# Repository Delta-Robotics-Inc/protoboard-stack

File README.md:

# Protoboard Stack

Protoboard is a framework for agents and people to design, check and release
hardware projects. A project describes its system in
[UHD](https://github.com/Delta-Robotics-Inc/uhd) (Universal Hardware
Description: modules, interfaces, links and harnesses, as TypeScript), and
Protoboard supplies the rest: project conventions, a parts library, checks,
a viewer, extensions that drive engineering tools (tscircuit and KiCad for
boards, build123d for CAD, Zephyr and ESP-IDF for firmware), skills that
teach an agent the workflow, and a release that ends in a Manufacturing
Package.

Think of it as "Next.js for hardware": initialize a project, add
capabilities as packages, work in VS Code with your agent, view the system
live, and cut a versioned hardware release. Any agent that speaks MCP or
reads `AGENTS.md` can use it; the stack does not run the agent.

This repository holds the stack: the framework core, the `protoboard` CLI,
the extensions, the viewer shells, the VS Code extension, the parts service
client, and the reference projects. It is open source under the [Apache
License 2.0](LICENSE).

## Install

Install the **Protoboard** extension in VS Code (Visual Studio Marketplace),
or in Cursor or Windsurf (Open VSX). It carries the whole stack and gives
your terminals the `protoboard` command, with no Node.js or npm needed. Or
install the command line alone (Node.js 22 or later):

```sh
npm i -g @protoboardai/cli
protoboard agents setup        # connect Claude Code, Codex, Cursor, … to the stack's MCP server
```

**[The installation guide](docs/guides/installation.md)** covers macOS,
Windows and Linux, each supported agent, your first project, signing in for
the Protoboard parts library (the only part that needs an account),
updating, uninstalling and troubleshooting.

## Quick start

```sh
protoboard init my-drone --template drone     # or wearable, iot; or a blank project
cd my-drone
protoboard check                              # every validator that can run; exit 1 on errors
protoboard dev --open                         # the viewer at http://127.0.0.1:5180/, live
protoboard release --check                    # what stands between the design and a release
```

Then open the folder in VS Code, or ask your agent to start from the
**build-a-project** skill. A project made with Protoboard 0.1 or 0.2 is moved
to 0.3 with `protoboard upgrade` ([release notes](docs/releases/stack-v0.3.md)).

## Documentation

- [Quickstart](docs/quickstart.md): a project from a template to a release, step by step.
- [Reference](docs/reference/README.md): the [CLI](docs/reference/cli.md),
  [configuration](docs/reference/configuration.md),
  [extensions and skills](docs/reference/extensions.md), the
  [Manufacturing Package format](docs/reference/manufacturing-package.md) and
  the [library protocol](docs/reference/library-protocol.md).
- Guides: [writing a capability provider](docs/guides/writing-a-capability-provider.md),
  [the SOP format](docs/guides/sop-format.md) every skill follows,
  [evals](docs/guides/evals.md), [a local registry](docs/guides/local-registry.md).
- Design: [architecture](docs/specs/architecture.md),
  [project structure](docs/specs/protoboard-project-structure.md),
  [UHD boundary](docs/specs/uhd-boundary.md),
  [tool integrations](docs/specs/tool-integrations.md),
  [distribution](docs/specs/distribution.md) and the rest of [docs/specs](docs/specs/).
- [Release notes](docs/releases/stack-v0.3.md).

## Repository layout

| Path | What |
| --- | --- |
| `packages/core` | `@protoboardai/core`: project loading, the definition registry, resolution, checks, build, templates, parts and libraries. |
| `packages/cli` | `@protoboardai/cli`: the `protoboard` command and its MCP server. |
| `packages/cloud` | `@protoboardai/cloud`: the typed client of the parts service and of any `uhd-library/v1` library. |
| `packages/views`, `packages/web-viewer` | The domain views and the shells of `protoboard dev` and the VS Code tabs. |
| `packages/ext-*` | The extensions: hardware, parts, sourcing, docs, release, drone, tscircuit, zephyr, esp-idf, frame-cad, harness-cad, enclosure-cad. |
| `packages/vscode-protoboard` | The VS Code extension ([developer reference](packages/vscode-protoboard/DEVELOPMENT.md)). |
| `examples/` | Reference projects: a 5-inch quadcopter, a wearable watch, a smart water bottle and a motor test bench. |
| `docs/` | The documentation above. |
| `scripts/` | CI, the lints, the local registry and publishing. |

## Developing

The stack builds against two repositories checked out beside it, UHD and the
viewer:

```sh
git clone https://github.com/Delta-Robotics-Inc/uhd.git
git clone https://github.com/Delta-Robotics-Inc/uhd-viewer.git
git clone https://github.com/Delta-Robotics-Inc/protoboard-stack.git
(cd uhd && npm install && npm run build)
(cd uhd-viewer && npm install && npm run build)
cd protoboard-stack && npm install
npm run typecheck && npm test
scripts/ci-stack.sh                 # the whole CI flow, as GitHub Actions runs it
```

[CONTRIBUTING.md](CONTRIBUTING.md) has the commands, the pull request
process and the sign-off; [docs/ci.md](docs/ci.md) the workflows.

## Licence and trademarks

The code is Apache-2.0 ([LICENSE](LICENSE), [NOTICE](NOTICE)); contributions
come in under the same licence with a DCO sign-off. "Protoboard" and its logo
are trademarks of Delta Robotics, Inc.; a fork you distribute needs its own
name ([TRADEMARKS.md](TRADEMARKS.md)).

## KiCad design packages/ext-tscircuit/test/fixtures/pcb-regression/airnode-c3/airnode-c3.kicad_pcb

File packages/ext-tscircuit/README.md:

# @protoboardai/ext-tscircuit

The first provider of the `circuit` capability
([tool integrations](../../docs/specs/tool-integrations.md)). It turns a UHD
board module into a routed PCB with [tscircuit](https://tscircuit.com), writes
the circuit capability's standard outputs, reads placements and frames back,
and checks the layout against the model. It runs inside Protoboard's own Node
process, offline.

A project selects it for one board, in the config next to the board module:

```ts
// src/boards/imu/circuit.config.ts
import { defineCapabilityConfig } from "@protoboardai/core";

export default defineCapabilityConfig({
  provider: "@protoboardai/ext-tscircuit",
  constraints: {
    layers: 2,
    thickness_mm: 1.0,
    outline: { circle: { diameter_mm: 30 } },
    mounting_holes: [{ id: "mount_left", at: [-11, -6], diameter_mm: 2.2 }],
    placements: { j1: { at: [0, 11.5], rotation_deg: 0 } }, // fixed by the enclosure
    keepouts: [{ name: "antenna", rect: { at: [0, -12], size: [8, 3] } }],
  },
});
```

```sh
protoboard run circuit:generate --module imu-tile-board
protoboard run circuit:export   --module imu-tile-board
protoboard run circuit:extract  --module imu-tile-board
protoboard check                # includes circuit:check for every bound board
```

The skill **circuit-board** (`skills/circuit-board/SKILL.md`) is the
procedure an agent follows: model the board, configure, generate, export,
extract, and act on each `CIRCUIT_*` finding.

`test/fixtures/imu-tile` is a complete example: an RP2040, a BMI270 and a
TPS63020 (test copies of UHD library parts in `test/fixtures/uhd-parts`, with
their origin noted there), with their decoupling, the regulator's inductor
and capacitors, and a JST SH header, on a 30 mm round board.

## How UHD maps to tscircuit

1. **Board netlist** (tool-neutral, in `@protoboardai/core`: `boardNetlist`).
   Each part on the board is a component with its UHD instance path, part
   id, kind, value, package facts and pin designators. A child that is a
   sub-module (`kind: "group"`, or children and no package or part number) is
   expanded: its parts are components under their paths (`led2/r1`), and its
   links join the board's (docs/specs/nested-boards.md); a child board or a
   daughterboard mated by connector stays off this PCB. Nets come from a
   union-find over the links of the board and its sub-modules between leaf
   pins and `Net` interfaces; a direct link between two functional ports
   (an I2C port to an I2C port) is copper, line by line as UHD pairs them.
   The board's exports are its edge. A KiCad or EasyEDA provider starts from
   the same step; only the land-pattern table and the writer differ.
2. **Source** (`lib/source.ts`). Each component becomes a `<chip>`,
   `<connector>`, `<resistor>`, `<capacitor>` or `<inductor>` named by its
   instance path. Its land pattern comes from the table below. Pad numbers are
   the part's designators; non-numeric ones (`EP`) follow the highest number.
   Each UHD pin is joined to its net by name (`<trace from=".u2 > .pin14"
   to="net.sda" />`). A pin with several pads (a module's grid of exposed
   ground pads) is one tscircuit port on its first pad and an internal port
   (`pinN_internal_k`) on each other pad; generate joins the pads to each other
   (see check), so every pad carries the net (`CIRCUIT_PAD_UNNETTED` otherwise). Supply, ground and no-connect pins get tscircuit pin
   attributes. Decoupling and pull-ups are components of the UHD board; the
   provider adds none.
3. **Constraints** (`lib/config.ts`). The outline (circle, rectangle or
   polygon; default: the board's `design_envelope`), mounting holes, keep-outs
   on each copper layer (an envelope keep-out takes `allow_bodies` from a
   config entry with its name and no shape), copper rules, and the positions the enclosure fixes
   (`pcbX`/`pcbY`/`pcbRotation`/`layer`; tscircuit does not move them). Later
   the enclosure's geometry manifest supplies the fixed positions.
   All of them are in the board frame (below), which is also the board
   module's own frame, so UHD regions on the board are read as they are. An
   outline taken from the `design_envelope` spans [0, length] × [0, width],
   the corner origin of UHD's example (`docs/boards-and-nets.md`). An envelope
   keep-out applies to each copper layer its z range reaches: top copper at
   z = +thickness/2, bottom at −thickness/2. A keep-out that misses the board,
   or reaches neither layer, is reported (`CIRCUIT_KEEPOUT`, warning) rather
   than silently doing nothing.
4. **Build** (`lib/runtime.ts`). The source is compiled with sucrase and
   rendered by `@tscircuit/core`: parts engine disabled, cloud autorouter off,
   a local autorouter preset (`auto_local` or `sequential_trace`). `fetch` is
   replaced during builds and exports by a guard that serves local files and
   refuses every network request.
5. **Stencil and silkscreen** (`lib/paste.ts`, `lib/silk.ts`), after every
   build. tscircuit prints paste at 70 % of each pad in each direction (49 %
   of its area), none on pill-shaped pads and on both sides of every plated
   hole; for every component with an authored land pattern those apertures
   are replaced by the pattern's own stencil (`paste`: 1:1 by default, a
   thermal pad's window-pane, none on bare test pads, pin-in-paste on plated
   slots on the part's side), placed and turned with the part. tscircuit draws
   silkscreen only for its built-in footprint strings, so each authored part
   also gets its reference (0.8 mm, else 0.6 mm, beside its courtyard where it
   clears every pad, hole, courtyard and the edge; a reference with no room is
   left off and logged) and a pin-1 dot. Paste apertures turned by other than a
   right angle are written to the paste Gerber as regions
   (circuit-json-to-gerber flashes them unrotated).

The provider directory, `src/boards/<module>/tscircuit/`:

| File | Owner | Content |
| --- | --- | --- |
| `board.gen.tsx` | generate (rewritten every time) | the generated source |
| `board.tsx` | you (written once) | the entry; wrap or replace the generated board here |
| `layout.json` | you | positions for parts the config does not fix: `{ <instance>: { at, rotation_deg, side } }` |
| `footprints.json` | you (optional) | land-pattern overrides: `{ packages: [entry…], instances: { <instance>: entry } }` |
| `circuit.json`, `build.json` | generate, export | the built board, the name map back to UHD, source and netlist digests, versions; `sourceFiles`, every file the build read besides the folder's own sources (JSON a hand file imports, a hand file in another folder), which the source digest covers |
| `models/` | export | box bodies for parts without a body artifact; copies of part bodies without their interface feature shapes |

**Bodies and supplier numbers in the source.** Generate writes each
component's body into `board.gen.tsx` as a `cadModel`: the part's STEP (the
copy in `models/` without its interface feature shapes), else its GLB or OBJ
(UHD GLBs are glTF metres, +Y up: `modelUnitToMmScale: 1000`,
`modelBoardNormalDirection: "y+"`), with the mount origin as
`modelOriginPosition`. Paths are relative to the `tscircuit/` folder with
forward slashes, so they mean the same on every OS and machine; no
`tsci dev` URL is ever written. tscircuit itself centres a model on the pads;
the provider's exports place every body by its mount frame on a copy of the
circuit JSON (below). Each component also gets `supplierPartNumbers` from the
offers the project holds (`parts/offers.json`, `parts/evidence/<part>/sourcing.json`),
for its own MPN, LCSC first (JLCPCB assembles from LCSC numbers), then DigiKey
and Mouser; they are generate inputs, so new offers make the board stale until
the next generate.

**Land patterns by package family.** An entry matches a package by its
normalised name, else by its family: `SOT-23-5`, `SOT23-5` and `SOT23-5L` are
one; `0402 (1005 metric) chip` is the 0402 chip; `QFN-32-EP`, `VQFN-32` and
`WQFN32` are `qfn-32`; `VSSOP-10` is `msop-10`. Either way every fact the entry
states (pin count, pitch, body size, maker) must agree. A family match is
reported (`CIRCUIT_FOOTPRINT_FAMILY`, info); a package whose name or family
has entries that do not fit is reported with why (`CIRCUIT_FOOTPRINT_MISMATCH`)
and generate stops on it, instead of picking one.

Parts missing from both the config and `layout.json` are placed by
tscircuit's packer. It fails on dense boards ("Unable to pack all PCB
components"), and placement errors stop routing; generate then fails and says
so. Add positions to `layout.json` and generate again.

## Standard outputs

Under `out/`, replaced by every export. The export writes into a staging
folder beside it (`.out.staging`), and core swaps the files in only when the
export succeeds: a failed export (a converter that throws) leaves the last
good `out/` in place, and nothing reading `out/` sees it half written:

| File | Content |
| --- | --- |
| `gerber/*.gbr`, `gerber/*.drl` | Gerber RS-274X with X2 attributes (copper, mask, paste, silk, `Edge_Cuts`) and Excellon (plated, non-plated). Creation timestamps are removed, so an unchanged board exports identical files. |
| `bom.csv` | `instance, part, name, kind, manufacturer, mpn, value, package, quantity, lcsc, supplier_part_numbers`, one row per component (`supplier_part_numbers`: `lcsc:C… digikey:… mouser:…`). tscircuit's own BOM lacks the MPN and is keyed by refdes, so it is not used. |
| `pnp.csv` | `instance, x_mm, y_mm, rotation_deg, side, part, mpn, package, lcsc`, at the pad bounding-box centre. |
| `jlcpcb/bom.csv`, `jlcpcb/cpl.csv` | The same parts in JLCPCB's assembly upload format, by reference designator (`refdes.json`, as the silkscreen prints them). BOM: `Comment, Designator, Footprint, LCSC Part #`, one row per part with its designators grouped; the LCSC number comes from the project's offers only and is left empty (and listed in the export's summary data, `withoutLcsc`) when there is none. CPL: `Designator, Mid X, Mid Y, Layer, Rotation`, mm with the unit, `Top`/`Bottom`, in the Gerbers' frame. Rotation is the layout's (counter-clockwise from the top): no correction for JLC's library orientation is applied, so check polarized parts in JLC's placement preview. A locked board writes them from KiCad's position file. |
| `board.glb` | glTF binary in glTF's own convention (metres, +Y up), like every other UHD body. One root node `board` maps tscircuit's frame to it; component nodes are named by instance path. |
| `board.step` | AP214, mm, board frame. One mapped item per component, named by instance path; model representations are named by artifact (`<part>#<artifact>`) or project-relative box path, and the header date is fixed, so an unchanged board exports an identical file. |
| `board.manifest.json` | UHD geometry manifest: `outline` (the underside), `board_top`, each mounting hole by its config id, each component by instance path, each board export by its id. Every feature also carries `frame` (origin, normal, xAxis). |
| `netlist.json` | `protoboard.netlist/v0`: the nets as the copper joins them, named by the UHD net each piece carries (`scl+sda` when a piece carries two). |
| `schematic.svg`, `pcb-top.svg`, `pcb-bottom.svg` | renders for the viewer. |

**Board frame:** mm, +X right and +Y up in the top view, +Z out of the top
copper, z = 0 on the board's mid-plane (tscircuit's convention). The top
surface is z = +thickness/2.

**Bodies** in `board.glb` and `board.step`, per component: the part's own UHD
body artifact (STEP), placed on the board by the part's mounting frame (the
interface facing −Z); else a box from the part's package facts
(`dimensions_mm`); else tscircuit's generated body for a built-in footprint,
or none. Export reports which one each component got, and names every body
`board.glb`'s converter could not load (it draws a box in its place; an
unfetched Git LFS file, say) instead of counting it as a body. Model files are
read through the offline guard, which takes absolute paths and `file://` URLs
on every platform (on Windows `C:\…`, `C:/…`, UNC paths and `file:///C:/…`). In both files a body's
origin goes to the footprint centre on the board surface (z = ±thickness/2).

UHD CAD bodies carry one named sub-shape per interface feature (thin marker
solids on the faces an interface binds to; for an SMD part, 0.25 mm under its
seating plane). They are not part of the body, so export writes a copy of the
part's STEP without the sub-shapes named after the part's interfaces, under
`models/`, and uses that.

`circuit-json-to-step` 0.0.43 places a model by recentring it on the bounding
box of every point in its file (axis placements included) and lifts it by
half the board thickness above a position that is already the board surface.
Export sets each mapped item's origin back to the component's position
afterwards, keeping the converter's axes. The test resolves every body's
world bounding box in `board.step` and checks it against the pick-and-place
centre and the board top.

## extract

Frames for the board's exports and interfaces, taken from the manifest
features of the same id: a connector's frame is its mouth, with the mating
direction as the normal; a component's is the top of its body; a pin export's
is its pad. A mechanical interface of the board binds to its underside. Also
the artifacts to reference (outputs and the native source, `format:
"tscircuit"`) and, outside UHD, the placements, outline and routing totals.
Writing frames into the module is a separate step, as for CAD.

## check

Pure: it reads the last build and writes nothing.

| Code | Severity | Finding |
| --- | --- | --- |
| `CIRCUIT_NOT_BUILT` | info | no build yet |
| `CIRCUIT_BOARD_GROUPING` | warning | a sub-module's export the board leaves unconnected (not marked `unconnected` on the child), or a sub-module with no parts |
| `CIRCUIT_STALE` | warning | the native source changed since the build (export rebuilds); the UHD board changed since generate; or `layout.json`, `footprints.json` or the config's constraints changed since generate (generate bakes them into `board.gen.tsx`, so only generate catches up; export says so in its summary); or `out/` was exported from other inputs than the current ones (the built board, what the board depends on in UHD, a body file, the provider's code, a converter version: `tscircuit/export.json` records what each export read, and the message names what changed), or by an earlier provider that kept no such record. What the board depends on is a projection of the board module: its components (part, name, maker, MPN, value, package, pins, bodies and mount frames, the interface ids stripped from bodies), nets, edge and the edge parts' mating frames, and its design envelope; descriptions, prices and documents are not in it, so editing them does not make `out/` stale. The constraints (outline, mounting holes, keep-outs) are fingerprinted with the config. Export is reproducible: the same inputs give the same `board.step` and `board.glb` |
| `CIRCUIT_DRC` | error | an error tscircuit recorded while building, or one `@tscircuit/checks` finds |
| `CIRCUIT_NET_OPEN`, `_SHORT`, `_EXTRA`, `CIRCUIT_UNROUTED`, `CIRCUIT_PIN_MISSING` | error | the copper's nets differ from the UHD nets (core's `netlistDrift`) |
| `CIRCUIT_PAD_UNNETTED` | error | a pin with several pads has pads the copper does not join to its net (boards generated before 0.1.7 netted only the first pad: the smart-bottle and wearable-watch ESP32-C3 ground pads) |
| `CIRCUIT_FINGERPRINT_FORMAT` | info | `tscircuit/export.json` is from a provider that fingerprinted the whole UHD module; such a record is not compared for the board (no false stale) until the next export writes the new format |
| `CIRCUIT_FOOTPRINT_FAMILY` | info | a land pattern chosen by the package's family, its facts agreeing |
| `CIRCUIT_FOOTPRINT_MISMATCH` | error | land patterns of the package's name or family exist but none fits its pin count, pitch or size (reported, not guessed) |
| `CIRCUIT_VIA_TOUCHING_PAD`, `CIRCUIT_VIA_UNDER_BODY` | error | a via whose ring touches an SMD pad / a via inside a courtyard, when `via_touching_pad` / `via_under_body` is `avoid` |
| `CIRCUIT_HOLE_CLEARANCE` | error | copper nearer a non-plated hole's wall than `rules.hole_clearance_mm`, or inside it; round holes are circles, pill holes stadiums, never bounding boxes |
| `CIRCUIT_TRACE_WIDTH` | warning | a net routed narrower than `trace_widths` asks |
| `CIRCUIT_COMPONENT_MISSING`, `_EXTRA` | error | a UHD component is not on the board, or the board has one UHD lacks |
| `CIRCUIT_OUTSIDE_OUTLINE` | error / warning | a pad off the board / a body overhanging the edge |
| `CIRCUIT_KEEPOUT` | error / warning | pads, traces or vias inside a keep-out on its layer / a keep-out off the board or reaching neither copper layer |
| `CIRCUIT_PLACEMENT_MOVED` | error | a part the config fixes is somewhere else |
| `CIRCUIT_FOOTPRINT_UNVERIFIED` | warning | a land pattern the board uses has no verification record against its maker's recommended land pattern, or its pads, pitch, rows, slots, holes, courtyard, paste or mask differ from the record (`verifyEntry`, below); the work order then opens with a hold |
| `CIRCUIT_VIA_RULES` | error | a via whose pad or drill is smaller than `rules.via_pad_mm` / `rules.via_drill_mm` (the router keeps to them; a via written by hand may not). A locked board's KiCad project carries the same minimums as custom rules (`<board>.kicad_dru`), so KiCad's DRC finds them too |
| `CIRCUIT_HAND_PAD_JOIN` | warning | a trace written by hand (in `board.tsx`) joins pads of one pin, which generate joins itself since 0.1.7; in KiCad it becomes copper on no net. Remove it. generate logs the same |
| `CIRCUIT_VIA_IN_PAD` | error / info | a via inside an SMD pad / the same with `via_in_pad: "fill_and_cap"` (the order asks for IPC-4761 type VII) |

Every finding carries a `location` (core's `DiagnosticLocation`): `at` (mm,
board frame) and `points` where it has several, the copper `layer`, and the
`components`, `pads` (circuit.json pad ids), `nets` and other copper `items`
(traces, vias, holes, pours, keep-outs) it concerns; a finding about the whole
board has `scope: "design"`. The PCB view draws findings there.

A pin with several pads (a module's grid of exposed ground pads) is joined pad
to pad by the shortest tree over the SMD pads: a join clear of the part's
other pads is straight copper laid on the built board after routing (so it
cannot change the routing), any other is a routed trace. A pin's plated holes
(a receptacle's shell stakes) are joined by the part's own metal and not by
copper.

A body overhanging the edge is judged by its courtyard as placed (turned
with the part), not its axis-aligned box; a part the native entry lets off the
board (`allowOffBoard`: a mid-mount receptacle in its cut-out) is not reported
for its body, and its pads still are.

The copper netlist is built from `pcb_*` elements only. The connectivity
map's full mode also merges the source intent, which would make an unrouted
net look connected (spike §4).

## Land-pattern table

`lib/land-patterns.ts` (the table), `lib/land-geometry.ts` (the entry format),
`lib/footprints.ts` (lookup and verification). UHD parts state their package
as the manufacturer prints it; which copper fits that package is the
provider's knowledge, kept here and never written into a part. An entry
matches a package by name, and when it says so by pin count, pitch, body size
and maker (`match.manufacturer`, a case-blind prefix of the part's
manufacturer: Murata and Yageo recommend different 0402 lands). Names are
compared without case, spaces, underscores or dashes, and `×` reads as `x`.
An entry's frame is the part's mounting frame, so the copper and the part's
3D body agree.

**Verification.** An authored entry carries a `verification` record: the
document, page and figure it was read from, the date, and the values the
drawing gives, transcribed independently of the pads: pad groups (pins, size
or a range the drawing allows, pitch, row spacing; `merged` for paired
contacts that share one land, drawn as two touching halves so each designator
has a pad), optionally every pad centre the drawing dimensions, plated slots
(drill and ring), round holes (plated with their pad, or not), each with the
centres the drawing puts them at (`at`, so a moved slot or peg is caught), the courtyard,
the stencil (margin, window counts and sizes, coverage, pins with none,
pin-in-paste) and the mask margin. `verifyEntry` compares the copper with the
record; an entry is verified when it has a record and nothing differs.
`circuit:check` reports every land pattern a board uses that is not verified
(`CIRCUIT_FOOTPRINT_UNVERIFIED`), and the board's work order states how many
are verified and opens with a hold while any is not. Built-in footprint
strings cannot be verified (their copper is not stated in the entry).

| Entry | Package (maker) | Drawing |
| --- | --- | --- |
| `yageo-rc0402-reflow` | 0402 (Yageo) | Chip Resistors Mounting, Table 1 |
| `murata-grm15-reflow`, `murata-grm18-reflow` | 0402, 0603 (Murata) | GRM specification sheets, Land Dimensions Table 2: one land inside both tolerance rows |
| `lga-14-3x2.5-p0.5-bosch` | LGA-14 3.0 × 2.5 (BMI270) | BST-BMI270-DS000-08 §8.3 |
| `vson-14-dsj-4x3-p0.5` | VSON-14 DSJ (TPS63020) | 4210895-2/E with its stencil (four windows on the thermal pad), 4208549-3/G |
| `ti-dbv0005a`, `ti-dgs0010a`, `ti-rsm0032b` | SOT-23-5, VSSOP-10, VQFN-32 (TI) | 4214839/K, 4221984/A, 4219108/B (thermal pad stencil 4 × 1.23 mm, 77 %) |
| `microchip-c04-2091-ot`, `microchip-c04-2123b-mc` | SOT-23-5, DFN-8 2 × 3 (Microchip) | C04-2091-OT Rev F, C04-2123B |
| `maxim-90-0065-tdfn8`, `maxim-90-0602-olga14` | TDFN-8 2 × 2, OLGA-14 (Analog Devices/Maxim) | land patterns 90-0065 rev E, 90-0602 rev F |
| `st-sot23-6l`, `st-vl53l4cd-lga12` | SOT23-6L, Optical LGA12 (ST) | DS4260 Figure 19; DS13812 Figure 19 (pads 1:1: ST gives no separate land) |
| `aos-sot23-po00001` | SOT23 (AOS) | PO-00001 rev N |
| `coilcraft-xfl4020`, `epson-fc-135`, `kingbright-aptf1616` | XFL4020, FC-135, APTF1616 | 745-3, FC-135_E_Ver2.0 [7], DSAO4453 |
| `alps-skrt-guide-bosses` | SKRT side-push switch (Alps) | SKRT catalog Drawing No.1 (guide-boss holes Ø0.9 NPTH) |
| `gct-usb4720-midmount`, `gct-usb4105-topmount` | USB-C receptacles (GCT) | USB4720 rev B, USB4105 rev B4 (plated stake slots, tag holes or peg holes, paired contacts on one land) |
| `espressif-esp32-c3-mini-1`, `raytac-mdbt50q` | modules | ESP32-C3-MINI-1 v2.2 Figure 11-1 (3 × 3 ground pads); MDBT50Q-1MV2 Ver. L §2.2 (every pad centre) |
| `eastrising-er-tft128-1-fpc` | ER-TFT1.28-1 FPC tail | the tail's contacts (the maker gives no board land) |
| `qfn-56-7x7-p0.4-ep3.2` | QFN-56 (RP2040, test fixture) | RP2040 datasheet Figure 167; no record yet (unverified) |
| `builtin-0201` … `builtin-1206`, `builtin-sot23`, `builtin-sot23_5`, `builtin-jst4_p1mm_sh` | chip passives and SOT-23 from makers with no entry; JST SH | tscircuit footprinter (built in); unverified |

Authored entries are lists of pads (designator, centre, size; top view, mm),
non-plated holes, plated holes and slots (`drill` in a pad), the courtyard
(`courtyard_mm`, centred on `courtyard_at`), the stencil (`paste`) and the
mask (`mask`). Where the drawing gives no courtyard, mask or stencil the
record says what was used (IPC-7351B nominal courtyard 0.25 mm beyond pads,
holes and body; NSMD mask 0.05 mm; paste 1:1). For built-in entries, generate
checks that the pattern has a pad for every pin designator. A project adds or
overrides entries in `tscircuit/footprints.json`, for a package or one
instance, with the same record (board copper designed in the project cites
the pad part that states it). A part with no package fact, or a package with
no entry, stops generate with a message saying which.

## Routing controls

Constraints in `circuit.config.ts`, beside `layers`, `rules` and `autorouter`:

| Constraint | Effect |
| --- | --- |
| `routing` | `on` (default) or `off`: the board is placed but not routed (`routingDisabled`). Check reports the unrouted nets, unconnected ports and unjoined pads as info, not errors: a placement-only board for review or a hand route |
| `trace_widths` | `{ nets?: { <UHD net id>: mm }, classes?: { signal?, power?, ground?: mm } }`: each net's `nominalTraceWidth` is its own width, else its class's, else the rules' (`power_trace_width_mm` for power and ground nets). A net id the board lacks stops generate. Check reports a net whose narrowest routed segment is narrower than asked (`CIRCUIT_TRACE_WIDTH`, warning: the router necks down where the width does not fit) |
| `via_in_pad` | `avoid` (default; the router keeps vias out of SMD pads, `isViaInPadAllowed` off) or `fill_and_cap` |
| `via_touching_pad` | `allow` (default) or `avoid`: no via ring touching an SMD pad it does not sit in. tscircuit's router has no such rule, so it is checked only (`CIRCUIT_VIA_TOUCHING_PAD`) |
| `via_under_body` | `allow` (default) or `avoid`: no via inside a component's courtyard. Checked only (`CIRCUIT_VIA_UNDER_BODY`) |
| `rules.hole_clearance_mm` | least distance from a non-plated hole's wall to any copper (pads, plated holes, vias, traces, pours). Checked (`CIRCUIT_HOLE_CLEARANCE`); without it, only copper inside a hole is reported. Round holes are circles, not bounding boxes |

## KiCad: preview, lock and unlock

KiCad is the final hand-placement step ([spec](../../docs/specs/pcb-kicad-handoff.md)):
tscircuit is the layout of record while the design changes, KiCad after a
person locks the board.

```sh
protoboard run circuit:kicad  --module <board>   # KiCad 10 project of the current build in tscircuit/kicad/ (a preview)
protoboard run circuit:lock   --module <board>   # the project into <board dir>/kicad/ + handoff.json: KiCad is the layout of record
protoboard run circuit:unlock --module <board>   # kicad/ to kicad-archive/<stamp>/; tscircuit again
```

The project (`lib/kicad/`): tscircuit's `circuit-json-to-kicad` 0.0.237 (MIT)
writes the board, schematic and project from `circuit.json`; the provider
renames components to their reference designators first and sets the part
bodies as export does, then edits the result: the board's own footprint and
symbol libraries (`<board>.pretty`, `<board>.kicad_sym`, `fp-lib-table`,
`sym-lib-table`), bodies copied to `3d/` and linked through `${KIPRJMOD}`,
`MPN`, `Manufacturer`, `LCSC` (from `parts/offers.json`), `UHD_Instance` and
`UHD_Part` on every symbol and footprint, symbols and footprints linked by
UUIDs derived from the instance paths, pads turned with their footprint,
mounting holes as board-only footprints `H1…`, pads that share a netted pad's
number given its net, KiCad's `unconnected-(…)` nets on unconnected pins, a
global label with the board's net on every connected schematic pin (the
converter's wires do not always reach the pins), the config's layers,
thickness, stack-up and edge clearance, and the board frame's origin as the
drill/place origin. `kicad-cli pcb upgrade` / `sch upgrade` then save both in
KiCad 10's format. On the smart-bottle board KiCad's DRC finds no
schematic-parity problem in the exported project, and its ERC only the
board's own power-flag findings.

Reference designators (`lib/kicad/refdes.ts`) are kept per instance in
`tscircuit/refdes.json`: an id that already reads as a designator of its
kind (`r3`) keeps it, others take the kind's prefix and the lowest free
number; a removed instance keeps its designator reserved.

After lock, `circuit:generate` refuses without `--force`, `circuit:export`
makes `out/` with `kicad-cli` (DRC first, into `out/drc.json`; an error stops
the export without `--force`; Gerber and Excellon, the position file re-keyed
by UHD instance, STEP and GLB with the part bodies, SVG renders, the copper
netlist; the BOM from the model; the manifest from the build at lock with
component positions from KiCad), and `circuit:check` compares the model, the
handoff record and the KiCad files (`CIRCUIT_LOCKED`, `CIRCUIT_KICAD_*`, spec
§4). Check runs `kicad-cli sch export netlist` on a copy when KiCad is
installed (it writes nothing into the project) and reads the board file
itself otherwise.

Known limits: the GLB and STEP from KiCad are in KiCad's frame (board bottom at
z = 0, not the mid-plane); a component turned in KiCad keeps tscircuit's
orientation in the manifest; footprints at angles other than right angles may
differ from their library copy (`lib_footprint_mismatch`, a warning).

## In the Manufacturing Package

With @protoboardai/ext-release, `protoboard release` calls `package:work-order`
(`ops/package.ts`) for each unit that builds a board this provider designs.
It adds the board's fabrication and assembly order: quantity, layers,
thickness, copper, surface finish, solder mask and silkscreen, the stack-up
for the layer count, assembly sides and placements from `out/pnp.csv`, the
leadless packages (from the parts' package names) that want a stencil and
X-ray inspection, and the files to send. These order values are optional
constraints in `circuit.config.ts`; the order marks the defaults it used:

| Constraint | Default |
| --- | --- |
| `copper_oz` | the fab's standard (1 oz outer) |
| `finish` | ENIG when any part is leadless (QFN, DFN, LGA, BGA, CSP, SON), else lead-free HASL |
| `solder_mask`, `silkscreen` | green, white |
| `assembly` | `fab` (the fab places from `pnp.csv`); `hand` |
| `fab_notes` | none: a list of notes for the fab, numbered on the order after the provider's own |
| `via_in_pad` | `avoid`: the router keeps vias out of SMD pads, and check reports any as an error; `fill_and_cap` allows them and adds the fill-and-cap note (IPC-4761 type VII) |

The order's own notes come first: a hold while any land pattern the board
uses is unverified (naming them), and the fill-and-cap note when vias sit in
pads under `via_in_pad: "fill_and_cap"`. It also states how many land
patterns are verified and how many vias are in pads.

They do not change the design, but they are inputs to it, so changing one
makes `check` report the board stale until it is regenerated. They are
validated with the other constraints (`copper_oz` a positive number;
`finish`, `solder_mask`, `silkscreen` non-empty strings; `assembly` exactly
`fab` or `hand`; `fab_notes` a list of non-empty strings): `generate` refuses a bad value and `check` reports it as
`CIRCUIT_CONFIG_INVALID`.
`test/package.test.ts` checks the order, and the release's bring-up checks
for a custom board, on the IMU tile.

## Licensing

- tscircuit's libraries are MIT, `@tscircuit/footprinter` ISC (the built-in
  footprint strings are generated locally by it), `circuit-to-svg` ISC.
  `@tscircuit/checks` publishes no licence field or file (spike, Versions).
- **KiCad footprint and 3D-model libraries are not bundled and not fetched.**
  They are CC-BY-SA 4.0; shipping converted footprints as a set inside this
  Apache-2.0 provider would mix a share-alike collection into it. The
  authored entries are drawn from the manufacturers' recommended land
  patterns instead. A user may add footprints they hold the rights to in
  their project's `footprints.json`.
- Component bodies come from the project's own UHD parts, or are boxes.
- `circuit-json-to-kicad` and `kicadts` are MIT (tscircuit). The KiCad skills
  (`kicad-layout-review`, `kicad-cli`) are derived from KiStack (MIT); see
  `NOTICE`. KiCad itself is not bundled: `kicad-cli` is a declared tool.

## Tools and versions

Declared as the tool `tscircuit-node` (`protoboard doctor` probes it with
`lib/probe.cjs`): every tscircuit package is pinned to an exact version in
`package.json`, because they release `0.0.x` versions daily. An upgrade is a
deliberate change, checked by this package's end-to-end test.

- `@tscircuit/core` 0.0.2056, `@tscircuit/checks` 0.0.233,
  `@tscircuit/footprinter` 0.0.430, `circuit-json-to-gerber` 0.0.111,
  `circuit-json-to-gltf` 0.0.141, `circuit-json-to-step` 0.0.43,
  `circuit-to-svg` 0.0.438, and core's peers at the spike's versions.
- `circuit-json-to-gerber` declares the `tscircuit` meta-package (with the
  `tsci` CLI) as a peer. The repository's `.npmrc` sets
  `legacy-peer-deps=true` so that npm does not install it: it is never run,
  and its own nested copies of `@tscircuit/core` broke module resolution in
  the workspace. Missing peers are listed in `package.json` instead.
- **Projects outside the workspace** (installed from the registry, without
  the repository's `.npmrc`) need the workspace's `legacy-peer-deps=true` in
  their own `.npmrc` (some tscircuit packages import `circuit-json` without
  declaring it, so it must be at the top level) and
  `"overrides": { "circuit-json": "0.0.510" }` in `package.json`
  (`@tscircuit/checks` and `@tscircuit/core` take it as a peer; an older
  hoisted copy stops the checks: `CIRCUIT_DRC` "@tscircuit/checks did not
  run"). The templates that use this extension write both; keep the override
  equal to the pin above (`packages/core/test/templates.test.ts` checks the
  templates and examples).
- **Node.** Developed on Node 24.14.1. The full contract (generate, export,
  extract, check of the test board) also passed on Node 22.23.3, although
  `circuit-to-svg` declares `engines.node: 24.x`.
- `tsci` and Bun are not used. tscircuit's route cache is not used either.
  Agents never run `tsci dev`, `tsci build` or `tsci export` on a board this
  provider owns: tsci rebuilds it with another core, re-routes it, and its
  watcher crashes on files generate and export rewrite (seen on a large field
  project). The
  Protoboard viewer shows `out/`. The skill's `references/pcb-workflow.md`
  has the workflow, how to get KiCad files until the provider writes them
 , and the fallback policy.
- One build of the test board (21 parts, 12 nets) takes about 35 s and 1.2 GB.

## Limits

- **Fabrication needs a second DRC.** tscircuit's rules are looser than a
  fab's; the spike found same-net vias 0.1 mm apart and exporter defects that
  only KiCad's DRC reports (spike §6). Defaults here are 0.15 mm traces and
  0.3/0.6 mm vias; review before ordering. Nothing is uploaded or ordered.
- **Routing quality.** Routes are complete, not tidy: detours and many vias.
  Hand polish belongs in `board.tsx` (`<tracehint>`, `<pcbtrace>`).
- **Placement** is hand-assisted: dense boards need `layout.json`.
  Bottom-side parts and model offsets on rotated parts are untested.
- **Bodies.** Only STEP body artifacts are used (GLB-only parts get a box). A
  part's mounting frame is assumed to face −Z with its X axis along the
  footprint's X.
- **Manifest `frame`.** UHD's `GeometryManifest` has no `frame` per feature
  yet; it is written as an extra field, proposed for UHD (spike §9).
- **Fixed placements** are written in the config today; reading them from the
  enclosure's manifest is the `cad` provider's follow-up.
- The test board is a routing and export load, not a reviewed design: see
  the fixture's header comment for what it leaves out.

## Evals

`evals/catch-swapped-nets`: the IMU tile's tscircuit source is hand-edited
(SDA and SCL swapped on the BMI270); the agent rebuilds the board, names the
fault and restores a board that matches the model. Its fixture builds the
board once and the solution twice (about 2 minutes, 1.2 GB per build). `evals/generate-imu-board`: a board never built, with a fault in its model to
catch first. `evals/announce-pcb-fallback`: KiCad files wanted today for a
hand finish, which the provider cannot write yet; the agent must announce
that it is leaving the official path, why and at what cost, record it in the
worklog and as feedback, and leave the model, `out/` and the provider's files
alone. Run them with `protoboard evals --extension tscircuit`; see the
[evals guide](../../docs/guides/evals.md).

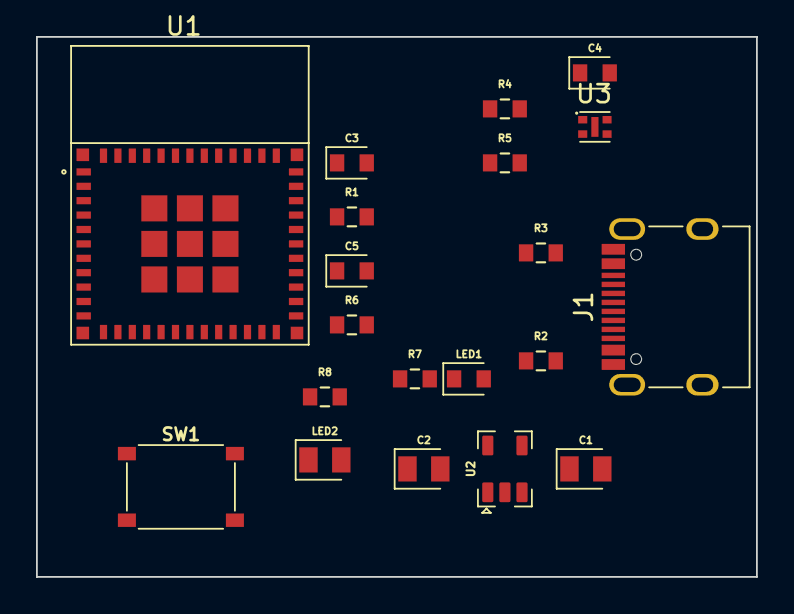
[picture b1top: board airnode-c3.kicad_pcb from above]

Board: 2 copper layers, 40.0 x 30.0 mm, 20 parts (0 on the bottom side), 15 nets, no tracks yet.

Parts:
C1, C2: 10uF; capacitor_cap0805
C3, C4: 100nF; capacitor_cap0603
C5: 1uF; capacitor_cap0603
J1: TYPE-C-31-M-12
LED1: LED; led_0603_color_red
LED2: LED; led_0805_color_green
R1, R6: 10kΩ; resistor_res0603
R2, R3: 5.1kΩ; resistor_res0603
R4, R5: 4.7kΩ; resistor_res0603
R7, R8: 1kΩ; resistor_res0603
SW1: SW1; TS-1187A-B-A-B
U1: ESP32-C3-MINI-1-N4
U2: AP2112K-3.3TRG1; AP2112K-3_3TRG1
U3: SHT40-AD1B-R2

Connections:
.J1 > .CC1 to .R2 > .pin1: J1.6, R2.1
.J1 > .CC2 to .R3 > .pin1: J1.12, R3.1
.R1 > .pin2 to .U1 > .EN: C5.1, R1.2, U1.8
.R6 > .pin2 to .U1 > .IO8: R6.2, U1.22
.R7 > .pin2 to .LED1 > .anode: LED1.1, R7.2
.R8 > .pin1 to .U1 > .IO7: R8.1, U1.21
.R8 > .pin2 to .LED2 > .anode: LED2.1, R8.2
.SW1 > .A to .U1 > .IO9: SW1.1, U1.23
GND: C1.2, C2.2, C3.2, C4.2, C5.2, J1.13, J1.14, LED1.2, LED2.2, R2.2, R3.2, SW1.3, U1.1, U1.2, U1.11, U1.14, U1.36, U1.37, U1.38, U1.39, U1.40, U1.41, U1.42, U1.43, U1.44, U1.45, U1.46, U1.47, U1.48, U1.49, U1.50, U1.51, U1.52, U1.53, U2.2, U3.4, U3.5
SCL: R5.1, U1.19, U3.2
SDA: R4.1, U1.18, U3.1
USB_DN: J1.7, J1.9, U1.26
USB_DP: J1.8, J1.10, U1.27
V3V3: C2.1, C3.1, C4.1, R1.1, R4.2, R5.2, R6.1, R7.1, U1.3, U2.5, U3.3
VBUS: C1.1, J1.15, J1.16, U2.1, U2.3

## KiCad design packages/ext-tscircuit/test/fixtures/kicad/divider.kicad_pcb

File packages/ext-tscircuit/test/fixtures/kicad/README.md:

# KiCad fixtures

Hand-written KiCad 10 files (board format 20260206, schematic 20260306) for
the KiCad handoff's unit tests (`test/kicad.test.ts`): a divider board,
`divider`, with a two-pin header `j1` (J1) and two 0402 resistors `r1` (R1)
and `r2` (R2) on nets `vin`, `mid` and `gnd`. Only what the readers use is
present: footprints with their fields and pads' nets, symbols with their
fields, and the netlist KiCad's `kicad-cli sch export netlist --format
kicadsexpr` writes for the schematic. KiCad itself is not needed to read
them.

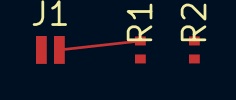
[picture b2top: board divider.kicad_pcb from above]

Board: 2 copper layers, 4 parts (0 on the bottom side), 3 nets.

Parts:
H1: hole_2.2mm
J1: SM02B-SRSS-TB; jst-sh-2
R1, R2: 10k; yageo-rc0402-reflow

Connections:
gnd: J1.2, R2.2
mid: R1.2, R2.1
vin: J1.1, R1.1
